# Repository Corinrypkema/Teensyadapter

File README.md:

Teensyadapter
=============

Teensy Adapter Board

Not much to say here yet.

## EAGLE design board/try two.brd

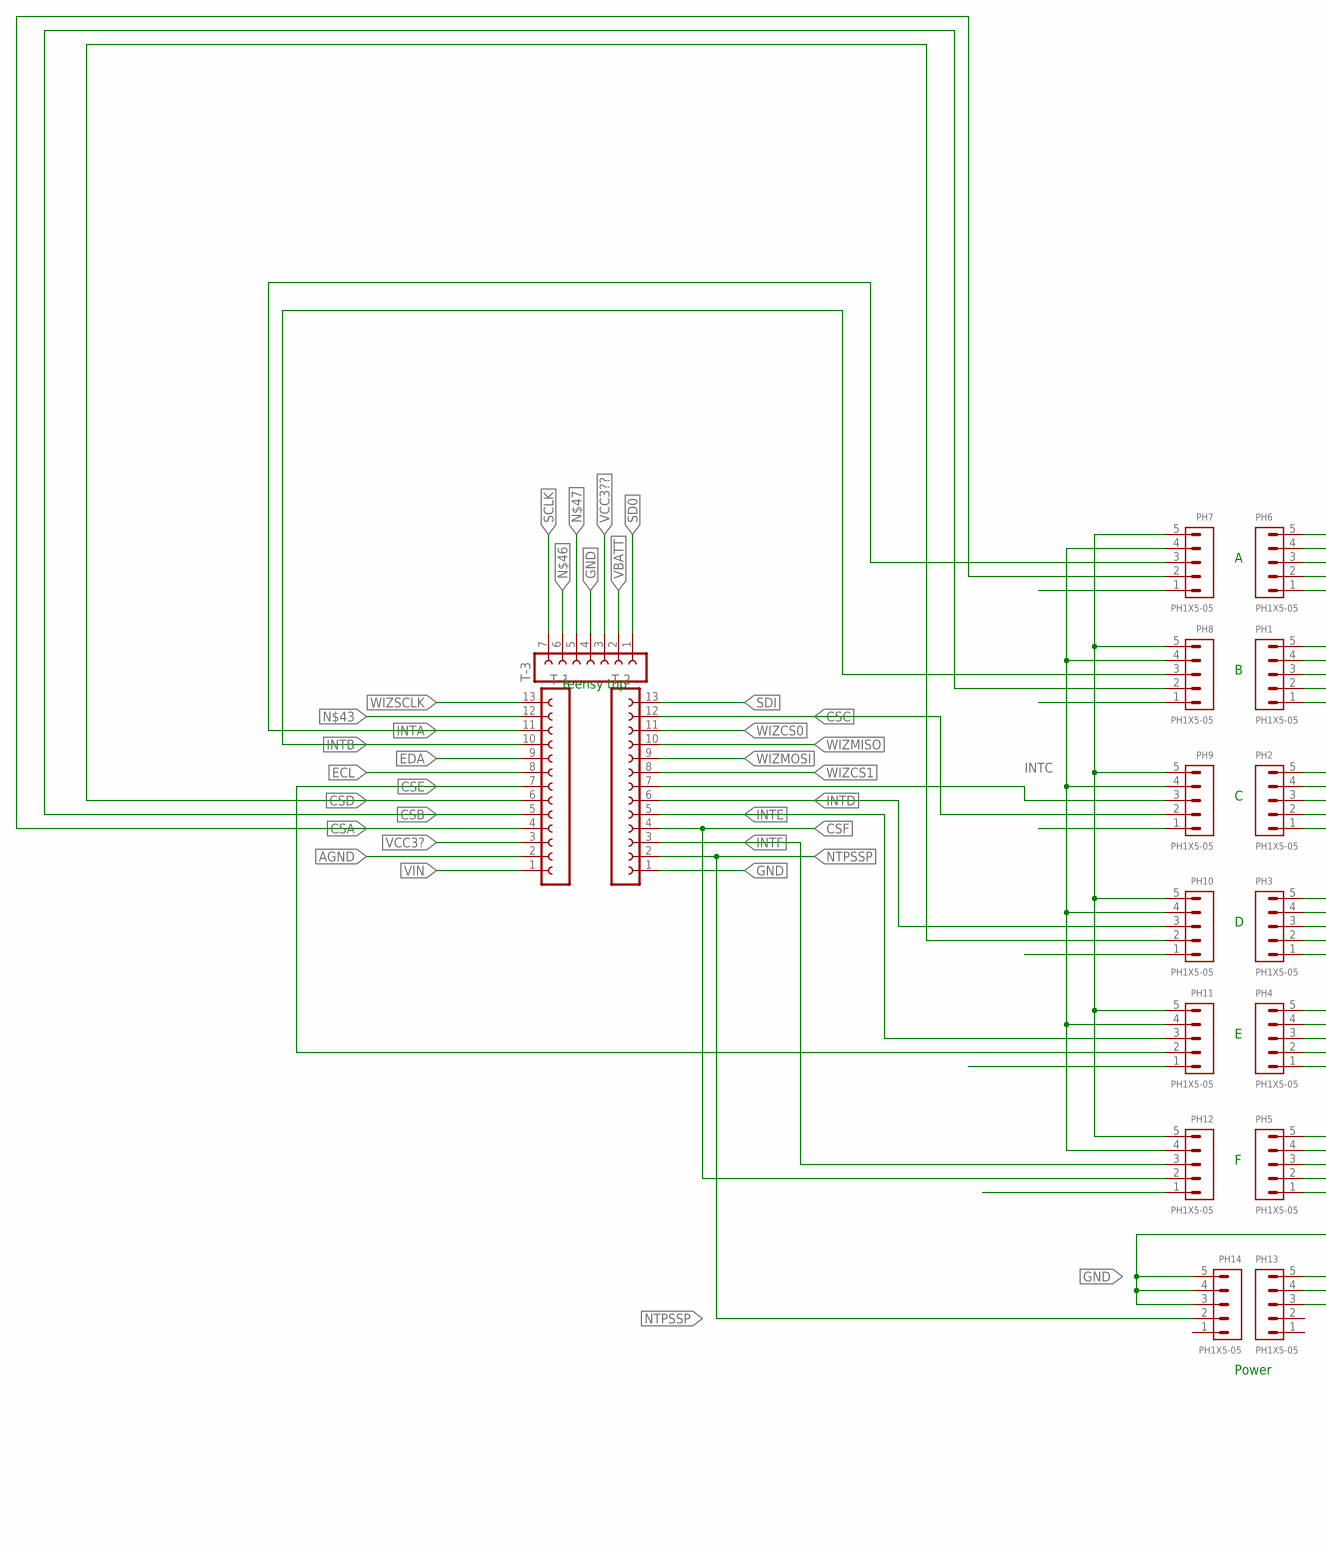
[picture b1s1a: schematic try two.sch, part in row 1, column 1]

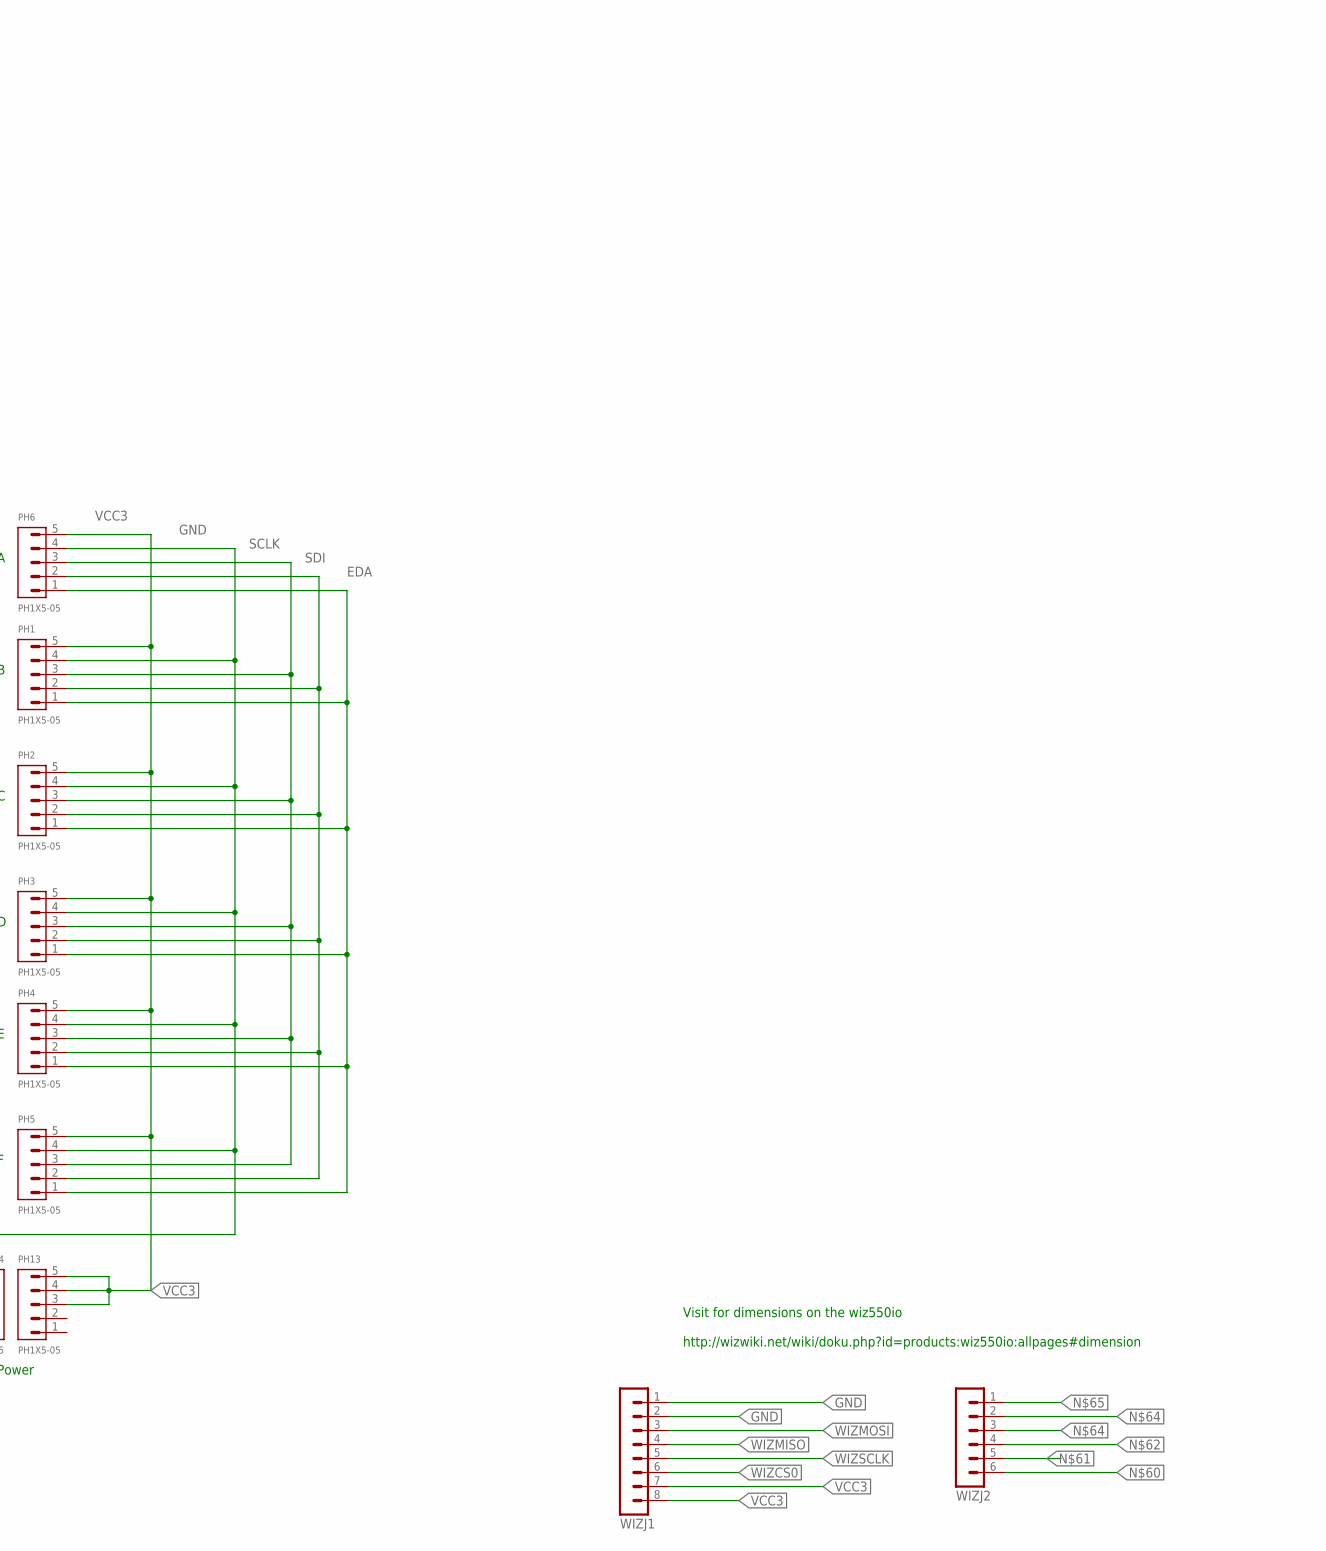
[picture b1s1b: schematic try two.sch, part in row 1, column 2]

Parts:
PH1, PH2, PH3, PH4, PH5, PH6, PH7, PH8, PH9, PH10, PH11, PH12, PH13, PH14: PH1X5-05; PH005-1-5
T-1, T-2: FE13-1; FE13
T-3: FE07-1; FE07
WIZJ1: MA08-1
WIZJ2: MA06-1

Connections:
AGND: T-1.2
CSA: PH7.2, T-1.4
CSB: PH8.2, T-1.5
CSC: PH9.2, T-2.12
CSD: PH10.2, T-1.6
CSE: PH11.2, T-1.7
CSF: PH12.2, T-2.4
ECL: PH7.5, PH8.5, PH9.5, PH10.5, PH11.5, PH12.5, T-1.8
EDA: PH1.1, PH2.1, PH3.1, PH4.1, PH5.1, PH6.1, T-1.9
GND: PH1.4, PH2.4, PH3.4, PH4.4, PH5.4, PH6.4, PH14.3, PH14.4, PH14.5, T-2.1, T-3.4, WIZJ1.1, WIZJ1.2
INTA: PH7.3, T-1.11
INTB: PH8.3, T-1.10
INTC: PH9.3, T-2.7
INTD: PH10.3, T-2.6
INTE: PH11.3, T-2.5
INTF: PH12.3, T-2.3
NTPSSP: PH14.2, T-2.2
SCLK: PH1.3, PH2.3, PH3.3, PH4.3, PH5.3, PH6.3, T-3.7
SD0: PH7.4, PH8.4, PH9.4, PH10.4, PH11.4, PH12.4, T-3.1
SDI: PH1.2, PH2.2, PH3.2, PH4.2, PH5.2, PH6.2, T-2.13
VBATT: T-3.2
VCC3: PH1.5, PH2.5, PH3.5, PH4.5, PH5.5, PH6.5, PH13.3, PH13.4, PH13.5, WIZJ1.7, WIZJ1.8
VCC3?: T-1.3
VCC3??: T-3.3
VIN: T-1.1
WIZCS0: T-2.11, WIZJ1.6
WIZCS1: T-2.8
WIZMISO: T-2.10, WIZJ1.4
WIZMOSI: T-2.9, WIZJ1.3
WIZSCLK: T-1.13, WIZJ1.5

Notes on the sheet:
Visit for dimensions on the wiz550io http://wizwiki.net/wiki/doku.php?id=products:wiz550io:allpages#dimension
teensy top
Power

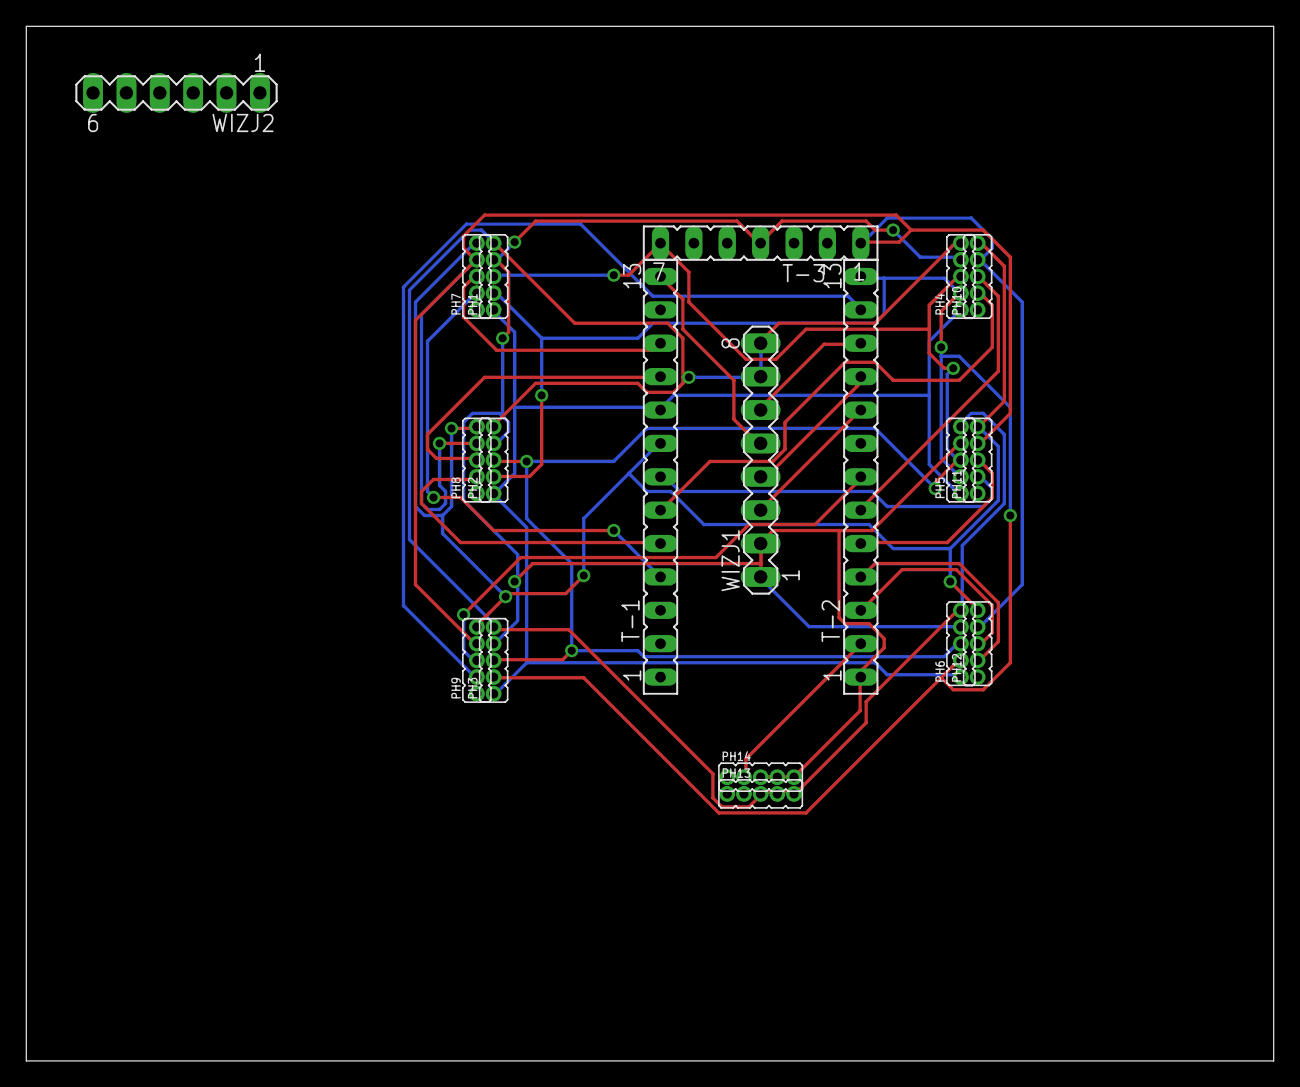
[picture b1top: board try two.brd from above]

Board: 2 copper layers, 94.9 x 78.7 mm, 19 parts (0 on the bottom side), 24 nets.

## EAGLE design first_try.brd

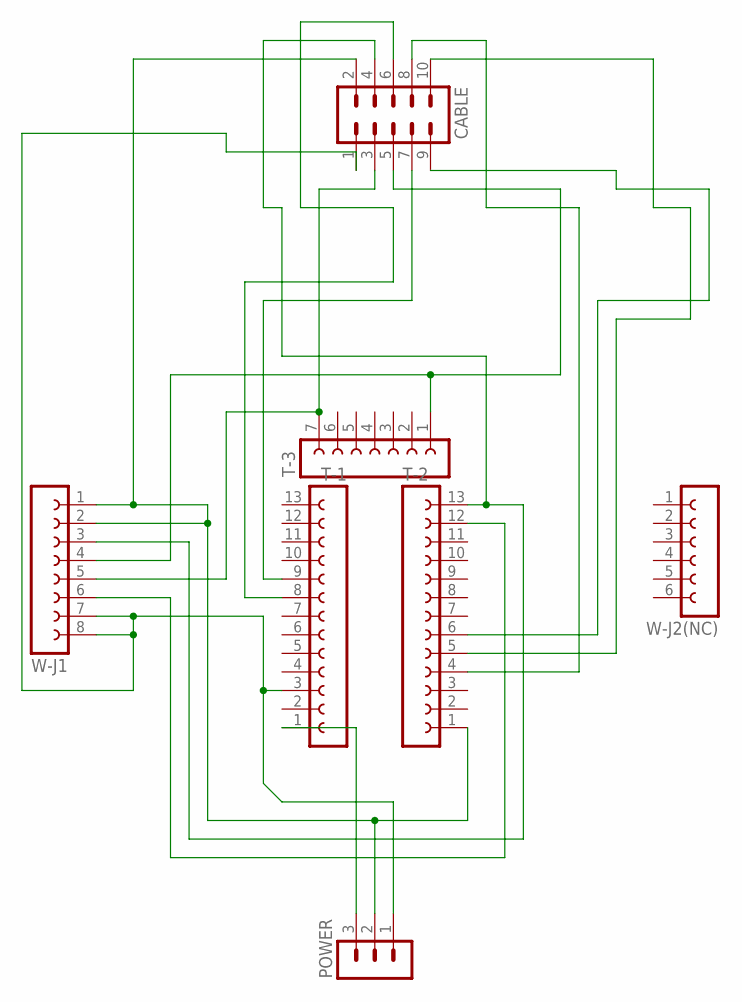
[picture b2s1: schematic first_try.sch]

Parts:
CABLE: MA05-2
POWER: MA03-1
T-1, T-2: FE13-1; FE13
T-3: FE07-1; FE07
W-J1: FE08-1; FE08
W-J2(NC): FE06-1; FE06

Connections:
3.3V: CABLE.1, POWER.1, T-1.3, W-J1.7, W-J1.8
GND: CABLE.2, POWER.2, T-2.1, W-J1.1, W-J1.2
MISO: CABLE.7, T-3.1, W-J1.4
MOSI: CABLE.4, T-2.13, W-J1.3
unnamed: CABLE.5, T-1.9
unnamed: CABLE.6, T-1.8
unnamed: CABLE.10, T-2.5
unnamed: CABLE.8, T-2.4
unnamed: CABLE.9, T-2.6
SCLK: CABLE.3, T-3.7, W-J1.5
SCSN: T-2.12, W-J1.6
V_IN: POWER.3, T-1.1

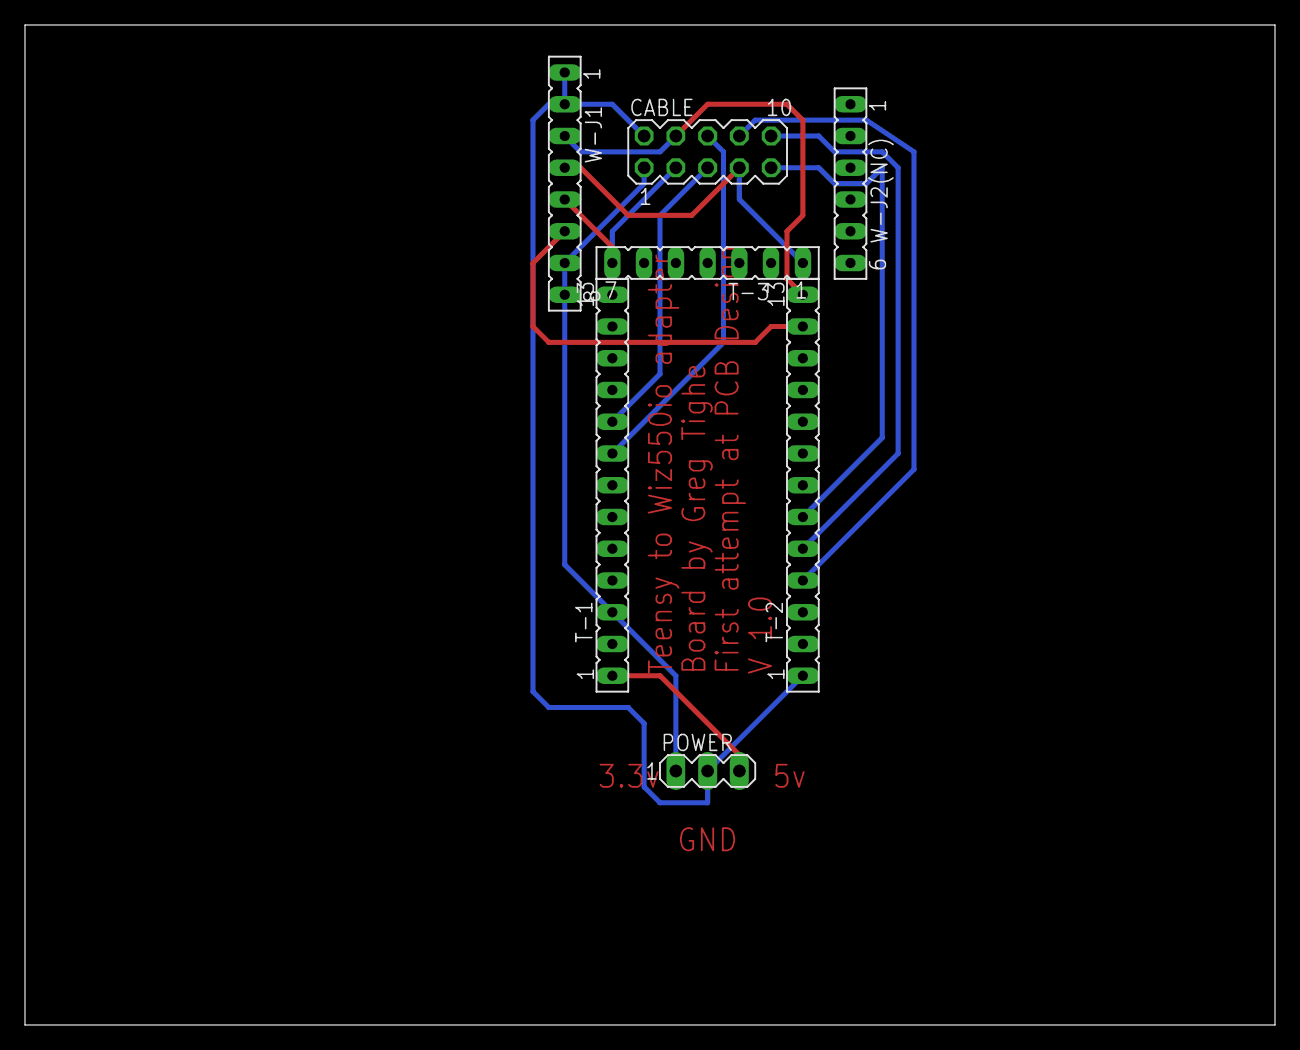
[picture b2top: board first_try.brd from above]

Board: 2 copper layers, 100.0 x 80.0 mm, 7 parts (0 on the bottom side), 12 nets.

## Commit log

2014-12-05 :boom::camel: Added .gitattributes
2014-12-05 First Commit
    Add init new files
2014-12-05 Structure changes
2014-12-05 Better routing
